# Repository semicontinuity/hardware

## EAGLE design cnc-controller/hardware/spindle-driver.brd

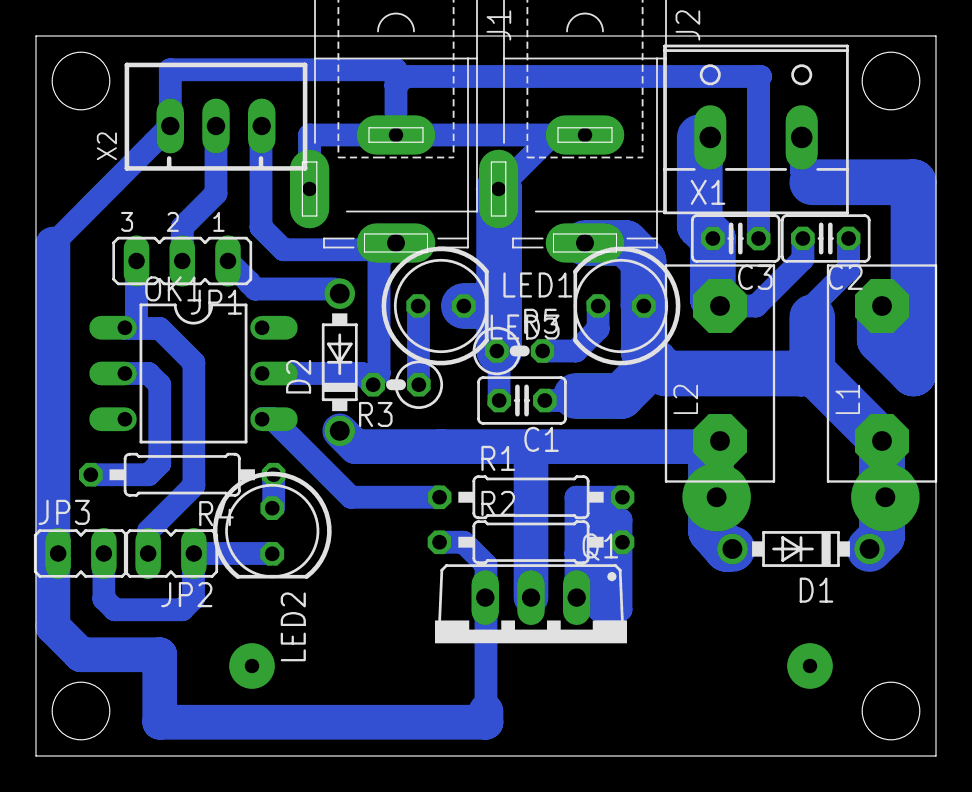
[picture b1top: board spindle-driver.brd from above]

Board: 2 copper layers, 50.0 x 40.0 mm, 24 parts (0 on the bottom side), 16 nets.

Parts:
C1, C2, C3: 0.1; C025-025X050
D1, D2: SB560; DO41-7.6
J1, J2: SPC4077
JP1: JP2
JP2, JP3: JP1
L1, L2: S11-10
LED1, LED2, LED3: LED5MM
OK1: 4N35; DIL06
Q1: IRF1405; TO220BV
R1: 10; 0207/10
R2: 10k; 0207/10
R3, R5: 0207/2V
R4: 200; 0207/10
X1: W237-132
X2: JST-XH-03-PIN-LONG-PAD; JST-XH-03-PACKAGE-LONG-PAD

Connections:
12V: J1.3, OK1.5, R3.2, X2.3
24V: C1.1, C2.1, D1.C, J2.3, L1.1, LED3.A
CONTROL: OK1.4, R1.1
D: D1.A, D2.C, L2.1, Q1.D
G: Q1.G, R1.2, R2.2
GND: C1.2, C3.1, J1.1, J1.2, J2.1, J2.2, JP3.1, LED1.K, Q1.S, R2.1, R5.1, X2.1
M+: L1.2, X1.2
M-: C2.2, C3.2, L2.2, X1.1
unnamed: LED3.K, R5.2
unnamed: D2.A, JP1.1
unnamed: LED2.A, R4.1
unnamed: OK1.2, R4.2
unnamed: LED1.A, R3.1
PWM+: JP1.3, JP2.2, OK1.1
PWM-: JP2.1, JP3.2, LED2.K
PWM_TTL: JP1.2, X2.2

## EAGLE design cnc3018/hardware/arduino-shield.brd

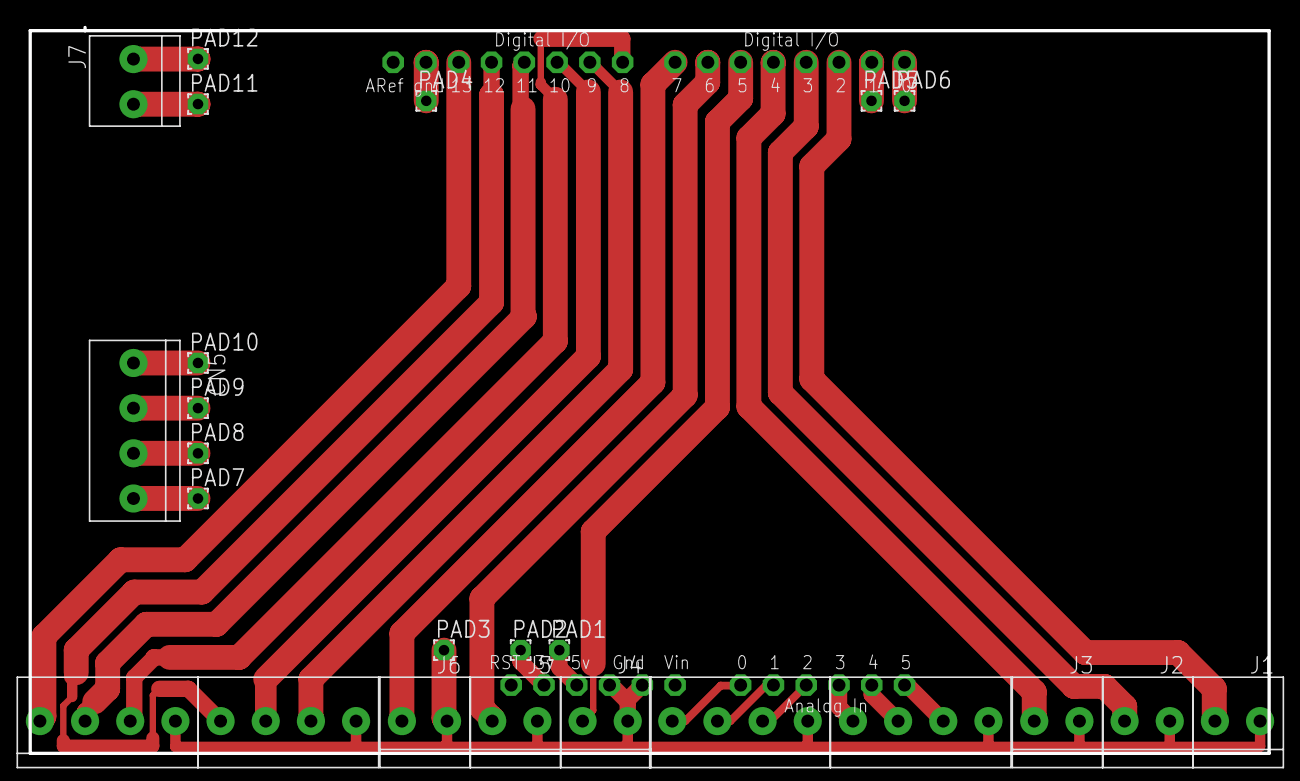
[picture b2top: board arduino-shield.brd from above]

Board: 2 copper layers, 96.0 x 56.0 mm, 25 parts (0 on the bottom side), 30 nets.

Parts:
CN1, CN2, CN3, CN4, CN5: 1X4-3.5MM; 1X04-3.5MM
J1, J2, J3, J4, J5, J6, J7: 1X2-3.5MM
PAD1, PAD2, PAD3, PAD4, PAD5, PAD6, PAD7, PAD8, PAD9, PAD10, PAD11, PAD12: 1,6/0,8
U$1: ARDUINO-NOHOLE

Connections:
A0: CN1.1, U$1.A0
A1: CN1.2, U$1.A1
A2: CN1.3, U$1.A2
A3: CN2.1, U$1.A3
A4: CN2.2, U$1.A4
A5: CN2.3, U$1.A5
D2: J1.2, U$1.D2
D3: J2.2, U$1.D3
D4: J3.2, U$1.D4
D5: J4.2, U$1.D5
D6: J5.2, U$1.D6
D7: J6.2, U$1.D7
D8: CN4.3, U$1.D8
D9: CN3.3, U$1.D9
D10: CN3.2, U$1.D10
D11: CN4.2, U$1.D11
D12: CN3.1, U$1.D12
D13: CN4.1, U$1.D13
GND: CN1.4, CN2.4, CN3.4, CN4.4, J1.1, J2.1, J3.1, J4.1, J5.1, J6.1, PAD3.1, U$1.GND1, U$1.GND2
unnamed: PAD2.1, U$1.3V
unnamed: PAD1.1, U$1.5V
unnamed: PAD6.1, U$1.D0
unnamed: PAD5.1, U$1.D1
unnamed: PAD4.1, U$1.GND
unnamed: J7.1, PAD12.1
unnamed: J7.2, PAD11.1
unnamed: CN5.1, PAD7.1
unnamed: CN5.2, PAD8.1
unnamed: CN5.3, PAD9.1
unnamed: CN5.4, PAD10.1

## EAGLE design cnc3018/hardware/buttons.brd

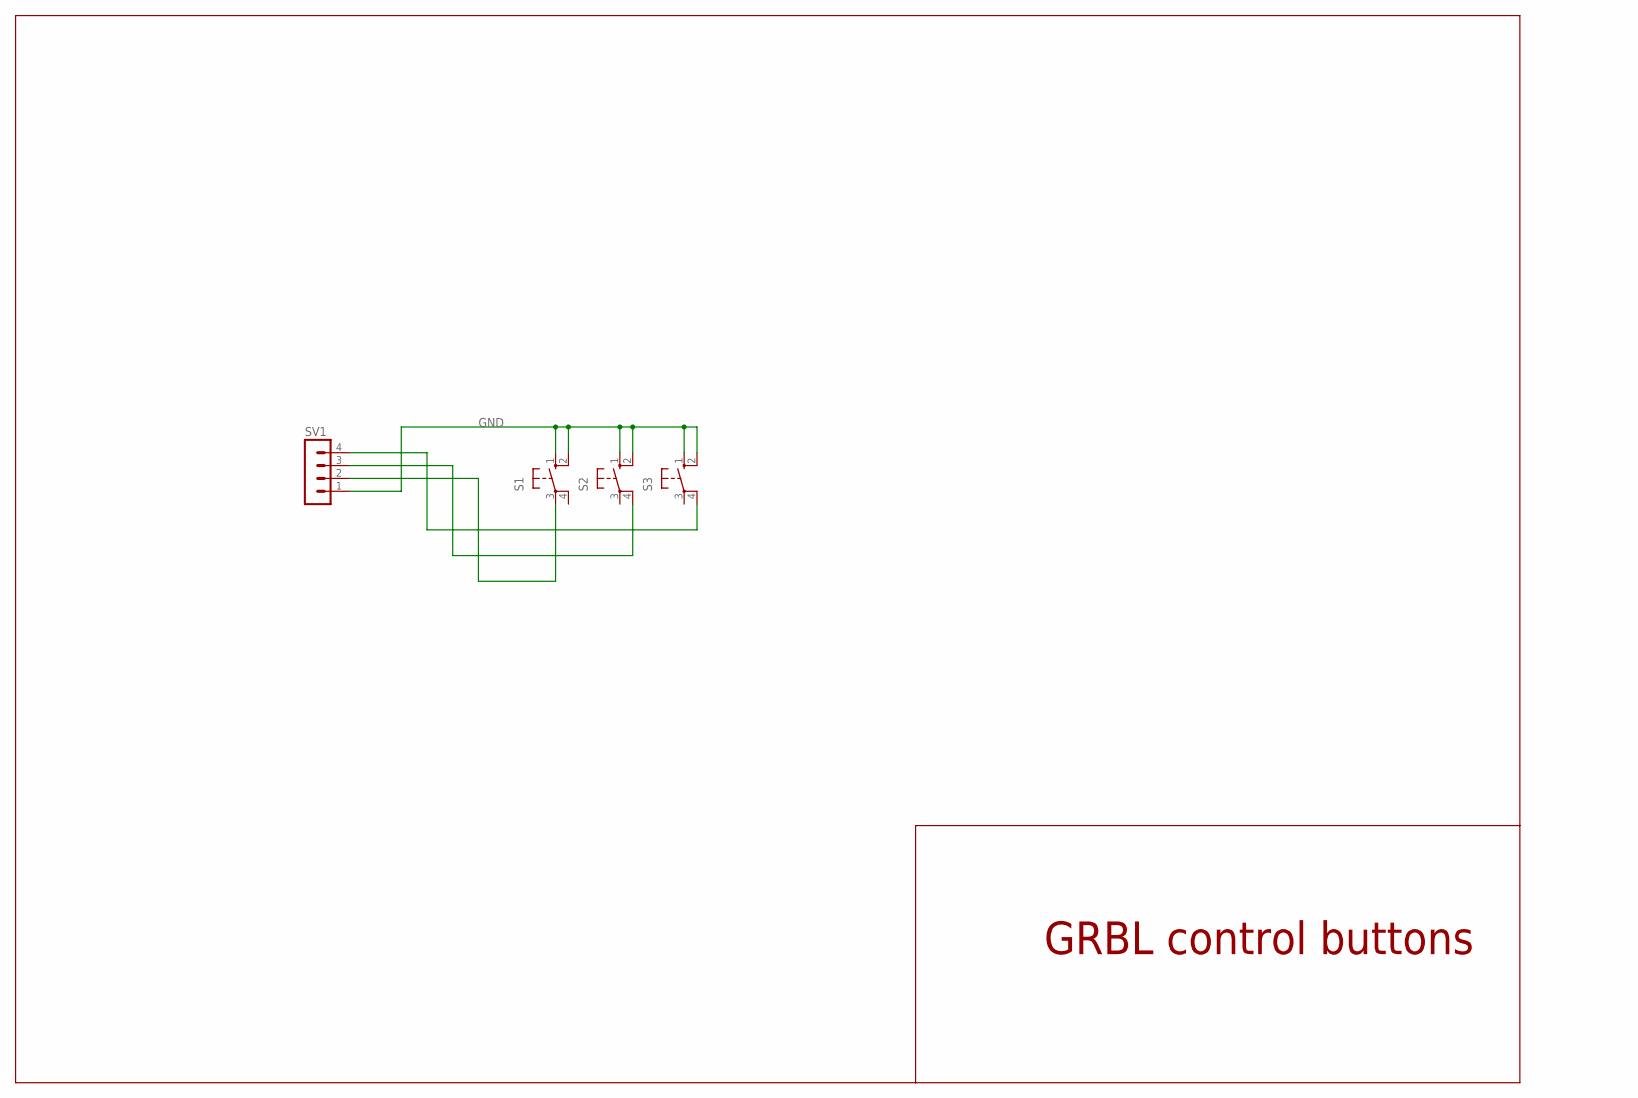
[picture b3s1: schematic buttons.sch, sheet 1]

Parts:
S1, S2, S3: 40-XX; B3F-40XX
SV1: MA04-1

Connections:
GND: S1.1 (S), S1.2 (S1), S2.1 (S), S2.2 (S1), S3.1 (S), S3.2 (S1), SV1.1
unnamed: S3.4 (P1), SV1.4
unnamed: S2.4 (P1), SV1.3
unnamed: S1.3, SV1.2

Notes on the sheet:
GRBL control buttons

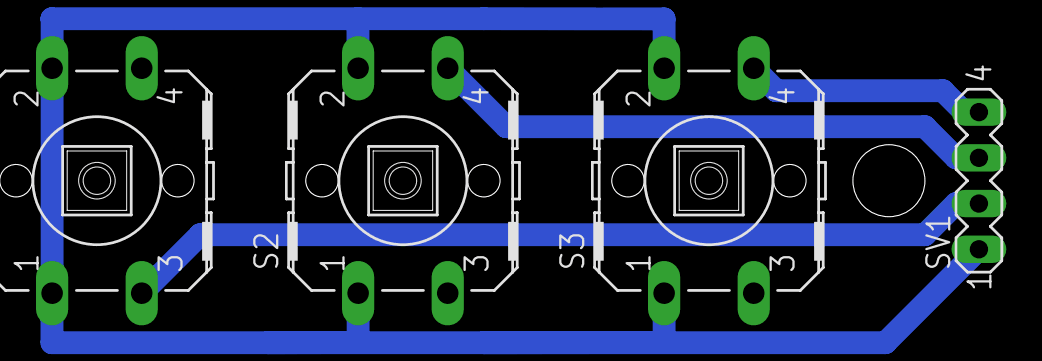
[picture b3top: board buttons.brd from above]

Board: 2 copper layers, 4 parts (0 on the bottom side), 4 nets.

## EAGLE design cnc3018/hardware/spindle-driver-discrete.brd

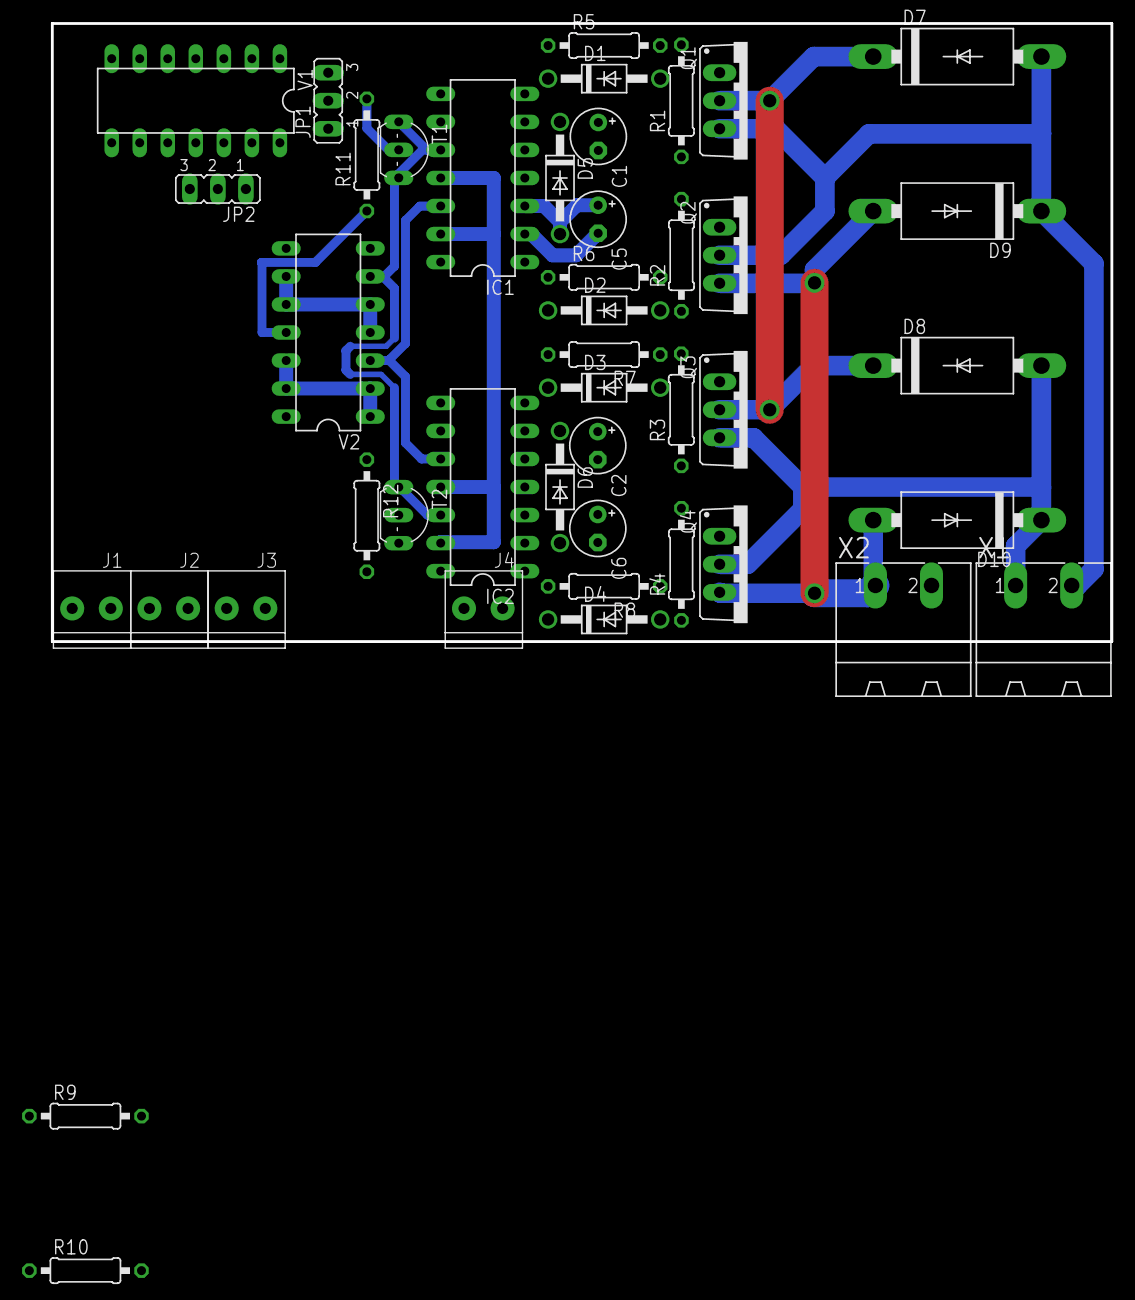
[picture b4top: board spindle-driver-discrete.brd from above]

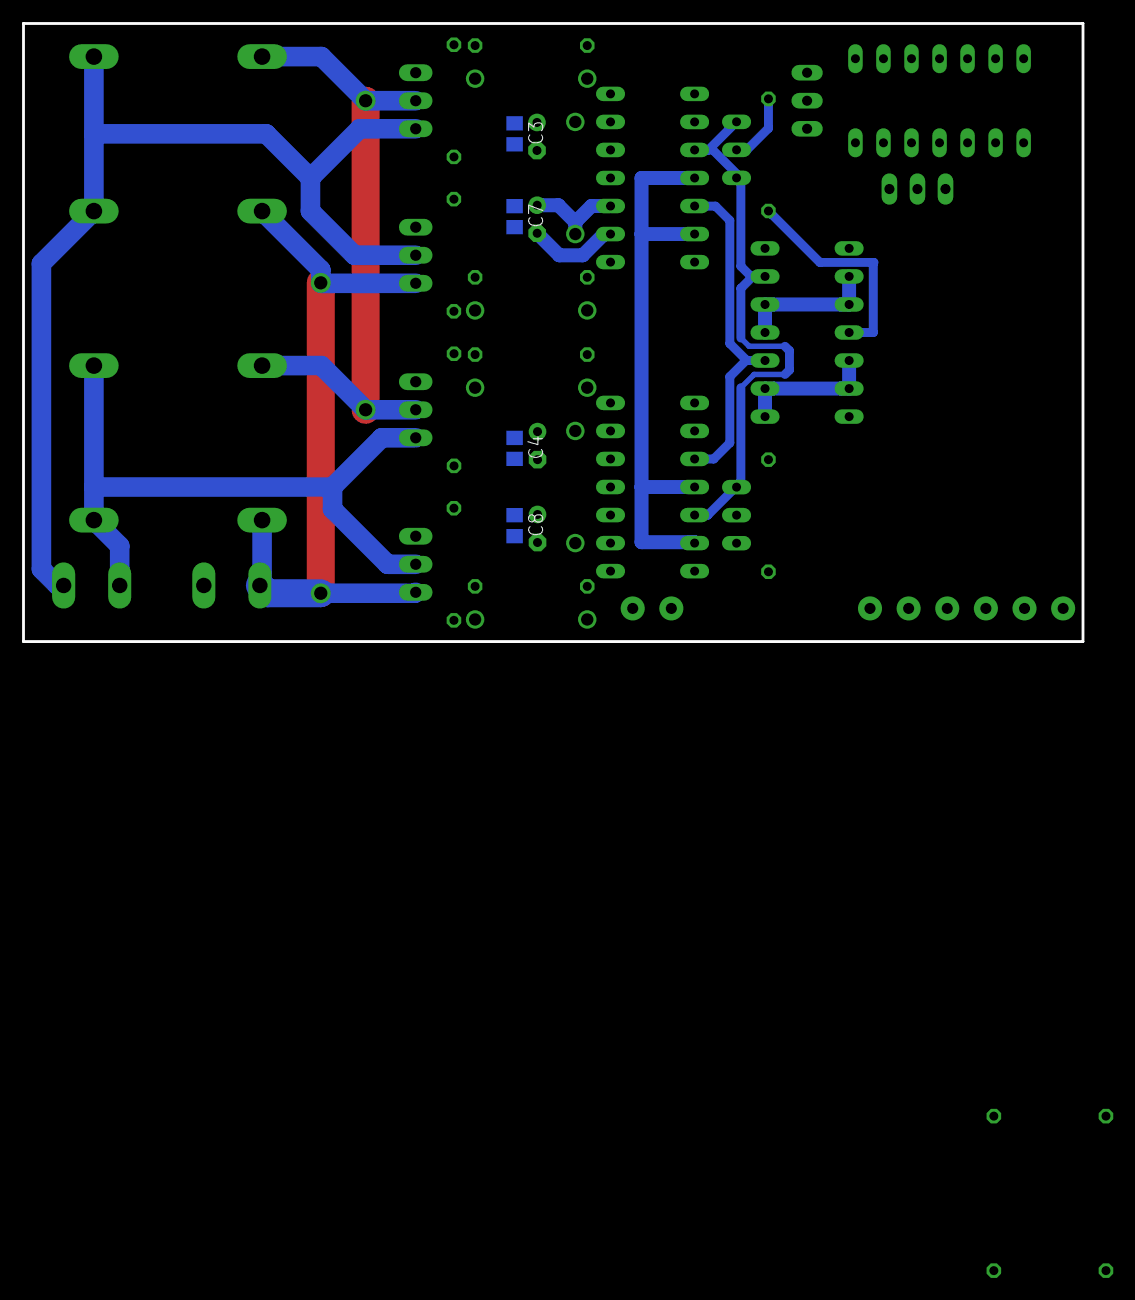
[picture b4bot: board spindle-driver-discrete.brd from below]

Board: 2 copper layers, 96.0 x 56.0 mm, 48 parts (4 on the bottom side), 32 nets.

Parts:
C1, C2: 20uF; E2,5-5
C3, C4, C7, C8: 100; C0805
C5, C6: 100uF; E2,5-5
D1, D2, D3, D4, D5, D6: UF4007; DO41-10
D7, D8, D9, D10: DO27-15
IC1, IC2: IR2110D; DIL14
J1, J2, J3, J4: 1X2-3.5MM
JP1, JP2: JP2
Q1, Q2, Q3, Q4: IRF1405; TO220BV
R1, R2, R3, R4, R9, R10: 0207/10
R5, R6, R7, R8: 10; 0207/10
R11, R12: 470; 0207/10
T1, T2: TO92-CBE
V1, V2: 74HC00N; DIL14
X1, X2: MSTBA2

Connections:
+UB: V1.14, V2.14
-UB: V1.7, V2.7
A: IC1.10, IC2.12, T1.C, V2.6
AGND: C5.-, C6.-, C7.2, C8.2, D9.A, D10.A, IC1.2, IC2.2, Q2.S, Q4.S, R2.1, R4.1, X2.1
AH: D1.C, IC1.7, R5.1
AL: D2.C, IC1.1, R6.1
AVCC: D7.C, D8.C, Q1.D, Q3.D, X2.2
B: IC1.12, IC2.10, T2.C, V2.3
BH: D3.C, IC2.7, R7.2
BL: D4.C, IC2.1, R8.2
DIR_B: JP2.1, V1.8, V1.13
GND: IC1.11, IC1.13, IC2.11, IC2.13, T1.E, T2.E
MOT_A: D7.A, D9.C, Q1.S, Q2.D, R1.1, X1.2
MOT_B: D8.A, D10.C, Q3.S, Q4.D, R3.1, X1.1
unnamed: JP1.2, V1.5
unnamed: JP2.2, V1.12
unnamed: D2.A, Q2.G, R2.2, R6.2
unnamed: D1.A, Q1.G, R1.2, R5.2
unnamed: D4.A, Q4.G, R4.2, R8.1
unnamed: D3.A, Q3.G, R3.2, R7.1
unnamed: V2.4, V2.5, V2.9, V2.10
unnamed: V2.1, V2.2, V2.12, V2.13
unnamed: R12.1, V2.8
unnamed: R11.1, V2.11
unnamed: R11.2, T1.B
unnamed: R12.2, T2.B
N_DIR_B: JP1.1, V1.9, V1.10
N_STEP_A: V1.1, V1.2
STEP_A: JP1.3, JP2.3, V1.3, V1.4
VB: D5.C, D6.C, IC1.6, IC2.6
VCC: C1.+, C2.+, C3.1, C4.1, C5.+, C6.+, C7.1, C8.1, D5.A, D6.A, IC1.3, IC2.3
VS: C1.-, C2.-, C3.2, C4.2, IC1.5, IC2.5

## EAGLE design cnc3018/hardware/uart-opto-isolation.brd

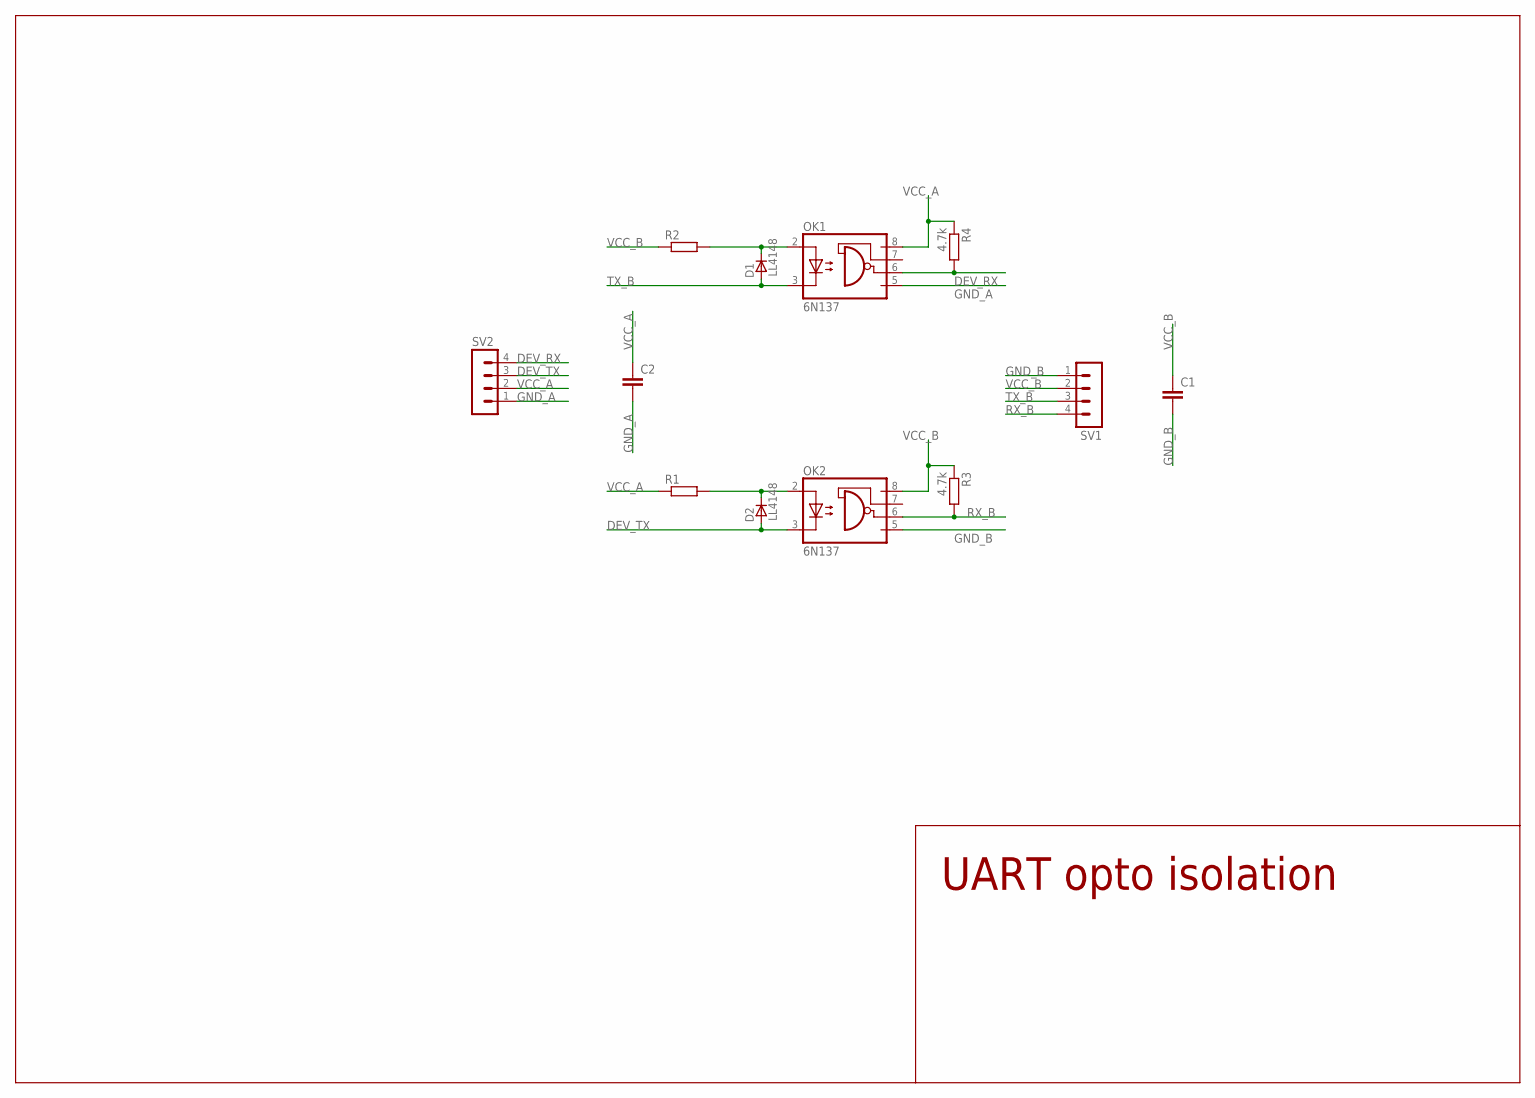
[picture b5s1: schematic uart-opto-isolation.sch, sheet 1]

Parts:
C1, C2: C-EUC0805; C0805
D1, D2: LL4148; SOD80_DO213AA_MINIMELF
OK1, OK2: 6N137; DIL08
R1, R2: R-EU_R0805; R0805
R3, R4: 4.7k; R0805
SV1, SV2: MA04-1

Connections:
DEV_RX: OK1.6 (VO), R4.2, SV2.4
DEV_TX: D2.A, OK2.3 (C), SV2.3
GND_A: C2.2, OK1.5 (GND), SV2.1
GND_B: C1.2, OK2.5 (GND), SV1.1
unnamed: D1.C, OK1.2 (A), R2.2
unnamed: D2.C, OK2.2 (A), R1.2
RX_B: OK2.6 (VO), R3.2, SV1.4
TX_B: D1.A, OK1.3 (C), SV1.3
VCC_A: C2.1, OK1.8 (VCC), R1.1, R4.1, SV2.2
VCC_B: C1.1, OK2.8 (VCC), R2.1, R3.1, SV1.2

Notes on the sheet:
UART opto isolation

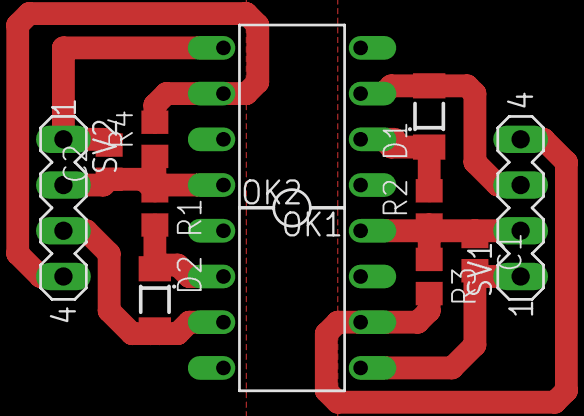
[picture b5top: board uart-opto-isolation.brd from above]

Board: 2 copper layers, 12 parts (0 on the bottom side), 10 nets.
